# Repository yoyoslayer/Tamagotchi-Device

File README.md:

# Photophage. A pet that feeds on light

## What it is
I made a special digitel pet that you can carry around with you. It is like the Tamagotchi toys from the 90s but I built it myself and custom made. The pet is on a screen that comes with pressable buttons a buzzer, a LED, and a sensor that can tell if it is in the light or dark. All of this is inside an egg-shaped case that I made using a 3D printer. The case also takes inspiration and certain design elements from the AniManga, Soul Eater.
What makes my tamagotchi unique is that it can tell what is going on in your environment. It has a sensor that can tell if it present in sunlight, indoor lighting or if it is dark so it will react to where it is and not just to what you do with the buttons.

## What it does / how to use it
- There are three buttons that you can use to take care of the pet: Feed, Play, Sleep.
- The pet has three things that you need to keep track of: Hunger, Happiness, Energy. These will go down over time so you need to check on the pet
If you press Feed, the pets Hunger will go up.
If you press Play, the pets Happiness will go up. Its Energy will go down a little bit.
If you press Sleep the pets Energy will go up.

- The pets face will change depending on how it's feeling. It will be happy if it is doing well okay if it is getting by and sad if something is wrong.
- There is a light that will change color depending on how the pet is feeling: green means it is happy amber means it is okay and red means it needs help.
- When you press a button the pet will make a beep.
- The pet can tell if it is in sunlight or indoor light and it will show you this every minutes. If it is dark it will not say anything.
- The pet runs on a battery that you can recharge and it lives in a custom egg-shaped case that I made.

## Assembly
1. Download CAD files from onshape and the gerber zip.
2. Purchase the parts from the BOM or select alternatives. (Screws must be exact identicals in dimensions)
3. Order the PCB from JLCPCB (or your prefferred vendor) using the gerber file attached
4. Print the case enclosure that houses the PCB and components
5. Cut velcro tape to reasonable sizes and attach one half to the Battery enclosure in the bottom case and the other half to the battery.
6. Attach, assemble, and solder the parts to the PCB as it looks according to the Onshape CAD
   - Be sure to check your battery connection after soldering
   - Solder the battery cell into the bottom side of the PCB rather than the top
   - The JST PH connector's wire will need to be shortened significantly to fit in the bottom case or wrapped neatly. Solder the connector into the battery cell.
7. Insert heat inserts into their respective mounting holes, place PCB, then screw in the screws
8. Repeat step 6 for the case
9. Assembly complete. YAYYY

## Why I made it
I made Photophage because I wanted to try something challenging. This was my 1st time building a whole project from scratch and I wanted to add some special features like the light sensor and the mood light. I chose to make it a virtual pet that feeds on light because I think it is a fun and interesting idea. I used this project to learn about all the parts of building an electronics project from designing the circuit board to writing the code and making the case. This serves as my first submission to the program Fallout, created by HackClub, an organization that promotes and encourages teens to become engineers/programmers.

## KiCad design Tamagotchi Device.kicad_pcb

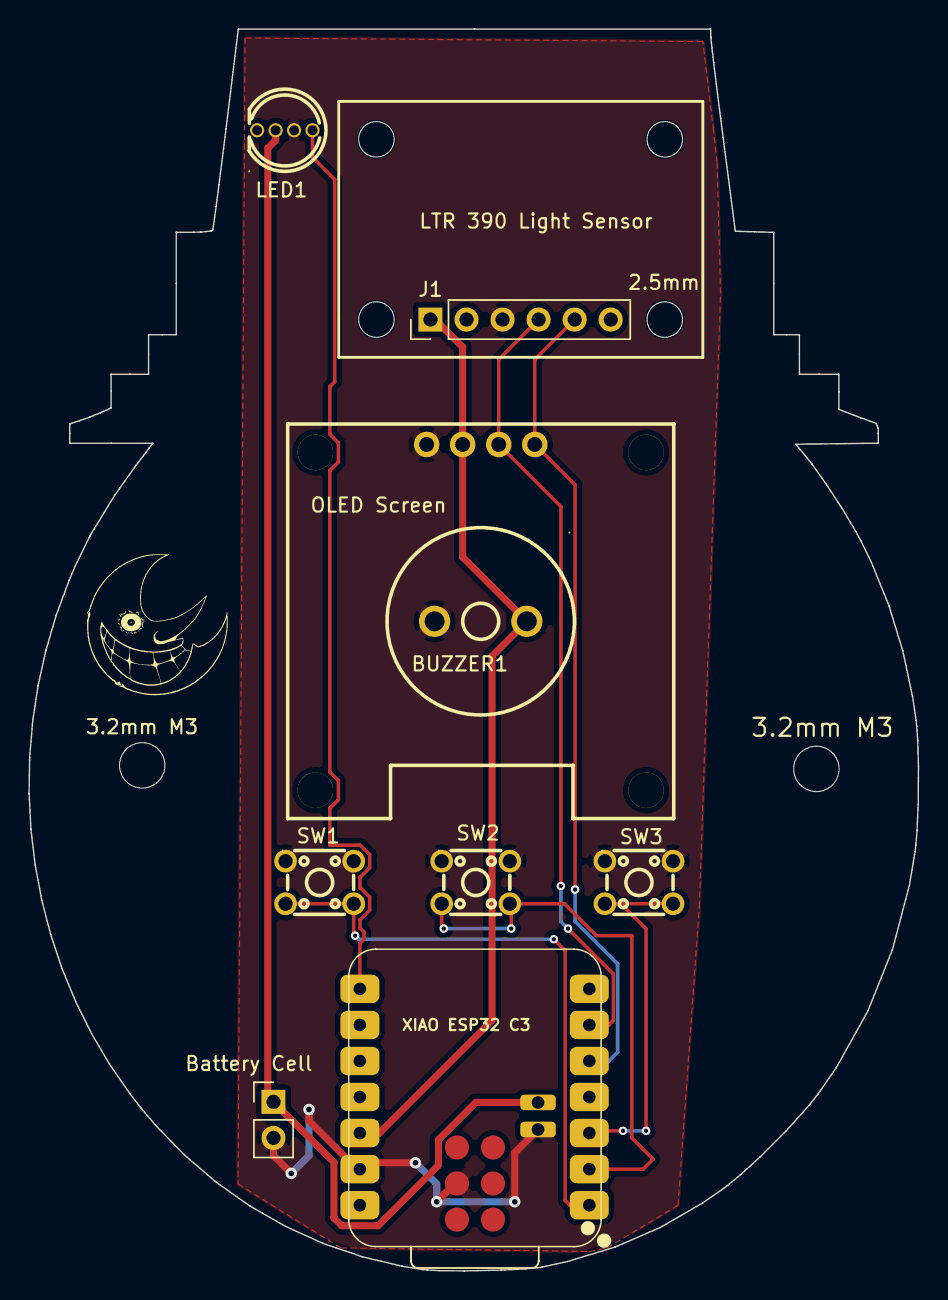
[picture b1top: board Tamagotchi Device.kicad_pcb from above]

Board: 2 copper layers, 62.7 x 87.5 mm, 12 parts (0 on the bottom side), 9 nets.

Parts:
2.5mm, 2.5mm#2: MountingHole_2.5mm
3.2mm M3: MountingHole_3.2mm_M3
BUZZER1: 1207-P6.5MM; BUZ-TH_BD12.5-P6.50-D1.4
Battery Cell: Battery_Cell; PinHeader_1x02_P2.54mm_Vertical
J1: Conn_01x06; PinHeader_1x06_P2.54mm_Vertical
LED1: WS2812D-F5; LED-TH_4P-BD5.8-P1.30
OLED Screen: HS96L03W2C03; OLED-TH_L27.8-W27.2-P2.54_C9900033791
SW1, SW2, SW3: SW_Push; SW-TH_4P-L4.5-W4.5-P3.00-LS4.8
XIAO ESP32 C3: XIAO-ESP32-C3-SMD

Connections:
+3V3: BUZZER1.1 (+), J1.1, OLED Screen.2 (VCC), XIAO ESP32 C3.12 (3V3)
+BATT: Battery Cell.1 (+), LED1.2 (VDD), XIAO ESP32 C3.15 (BAT)
GND: BUZZER1.2 (-), Battery Cell.2 (-), J1.3, LED1.3 (GND), OLED Screen.1 (GND), SW1.1, SW2.1, SW3.1, XIAO ESP32 C3.13 (GND), XIAO ESP32 C3.16 (GND), XIAO ESP32 C3.20 (GND)
unnamed: J1.4, OLED Screen.3 (SCL), XIAO ESP32 C3.6 (GPIO7_D5_SCL)
unnamed: J1.5, OLED Screen.4 (SDA), XIAO ESP32 C3.5 (GPIO6_D4_SDA)
unnamed: LED1.4 (Din), XIAO ESP32 C3.8 (GPIO20_D7_RX)
unnamed: SW1.2, XIAO ESP32 C3.1 (GPIO2_A0_D0)
unnamed: SW2.2, XIAO ESP32 C3.2 (GPIO3_A1_D1)
unnamed: SW3.2, XIAO ESP32 C3.3 (GPIO4_A2_D2)

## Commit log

2026-06-13 Add files via upload
    Screenshots of Front and Back of 3D View
2026-06-13 Add link to Bill of Materials spreadsheet
2026-06-20 Add files via upload
    Photophage Zine
2026-06-21 Reorganizing files
2026-06-22 Renaming and Zine Fixes
2026-06-23 Add MIT License with copyright notice
2026-06-25 Revise assembly steps in README for clarity
    Updated assembly instructions for battery attachment and soldering.
